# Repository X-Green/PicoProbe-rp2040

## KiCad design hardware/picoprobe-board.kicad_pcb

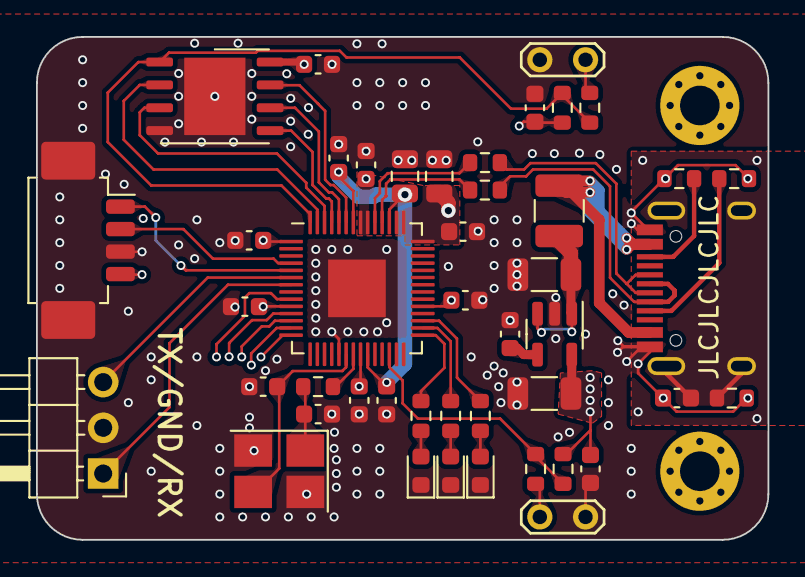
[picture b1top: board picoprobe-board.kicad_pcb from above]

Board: 4 copper layers, 40.6 x 27.9 mm, 47 parts (0 on the bottom side), 35 nets.

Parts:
C1, C2, C5, C6, C7, C8, C9, C10, C11, C12: 100nF; C_0603_1608Metric
C3: 1uF; C_0603_1608Metric
C4, C14: 2.2uF; C_0805_2012Metric
C15: 10uF; C_1206_3216Metric
C16, C18: 10nF; C_0603_1608Metric
C17: 2.2uF; C_1206_3216Metric
C19, C20: 12pF; C_0603_1608Metric
D1, D2, D3: LED; LED_0603_1608Metric
F1: Fuse; Fuse_1210_3225Metric
H1, H2: MountingHole_Pad; MountingHole_2.2mm_M2_Pad_Via
J1: Conn_01x03_MountingPin; PinHeader_1x03_P2.54mm_Horizontal
J2: USB_C_Receptacle_USB2.0; USB_C_Receptacle_HRO_TYPE-C-31-M-12
J3: Conn_01x04_MountingPin; Molex_PicoBlade_53261-0471_1x04-1MP_P1.25mm_Horizontal
JP1, JP2: Jumper_2_Open; TestPoint_2Pads_Pitch2.54mm_Drill0.8mm
R1, R3: 10K; R_0603_1608Metric
R2, R4: 1K; R_0603_1608Metric
R5: 470R; R_0603_1608Metric
R6, R7: 27.4R; R_0603_1608Metric
R9, R10, R11: 4.7K; R_0603_1608Metric
R14, R15: 5.1k; R_0603_1608Metric
R16: 1M; R_0603_1608Metric
U1: W25Q32JVZP; WSON-8-1EP_6x5mm_P1.27mm_EP3.4x4.3mm
U2: RP2040; QFN-56-1EP_7x7mm_P0.4mm_EP3.2x3.2mm
U3: RT9013-33GB; TSOT-23-5
Y2: Crystal_GND24; Crystal_SMD_3225-4Pin_3.2x2.5mm_HandSoldering

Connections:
+3V3: C1.2, C2.1, C3.2, C7.2, C8.2, C9.2, C10.2, C11.2, C12.2, C14.2, C17.1, J3.4, R1.1, R3.1, U1.8 (VCC), U2.1 (IOVDD), U2.10 (IOVDD), U2.22 (IOVDD), U2.33 (IOVDD), U2.42 (IOVDD), U2.43 (ADC_AVDD), U2.44 (VREG_IN), U2.48 (USB_VDD), U2.49 (IOVDD), U3.5 (VOUT)
+5V: C15.1, F1.1, U3.1 (VIN), U3.3 (EN)
/QSPI_CLK: U1.6 (CLK), U2.52 (QSPI_SCLK)
/QSPI_SD0: U1.5 (DI(IO0)), U2.53 (QSPI_SD0)
/QSPI_SD1: U1.2 (DO(IO1)), U2.55 (QSPI_SD1)
/QSPI_SD2: U1.3 (IO2), U2.54 (QSPI_SD2)
/QSPI_SD3: U1.7 (IO3), U2.51 (QSPI_SD3)
/QSPI_SS: R1.2, R2.2, U1.1 (~CS), U2.56 (QSPI_SS)
/RUN: R3.2, R4.1, U2.26 (RUN)
/SWCLK: J3.2, U2.4 (GPIO2)
/SWDIO: J3.1, U2.5 (GPIO3)
/UART1_RX: J1.1, U2.7 (GPIO5)
/UART1_TX: J1.3, U2.6 (GPIO4)
/USB_DM: J2.A7 (D-), J2.B7 (D-), R7.1
/USB_DP: J2.A6 (D+), J2.B6 (D+), R6.1
/VREG: C4.2, C5.2, C6.2, U2.23 (DVDD), U2.45 (VREG_VOUT), U2.50 (DVDD)
GND: C1.1, C2.2, C3.1, C4.1, C5.1, C6.1, C7.1, C8.1, C9.1, C10.1, C11.1, C12.1, C14.1, C15.2, C16.2, C17.2, C18.1, C19.2, C20.2, D1.1 (K), D2.1 (K), D3.1 (K), J1.2, J2.A1 (GND), J2.A12 (GND), J2.B1 (GND), J2.B12 (GND), J3.3, J3.MP (MountPin), JP1.1 (A), JP2.1 (A), R14.1, R15.1, R16.1, U1.4 (GND), U1.9 (EP), U2.19 (TESTEN), U2.57 (GND), U3.2 (GND), Y2.2, Y2.4
unnamed: C20.1, R5.1, Y2.1
unnamed: D1.2 (A), R9.1
unnamed: D2.2 (A), R10.1
unnamed: D3.2 (A), R11.1
unnamed: F1.2, J2.A4 (VBUS), J2.A9 (VBUS), J2.B4 (VBUS), J2.B9 (VBUS)
unnamed: J2.A5 (CC1), R14.2
unnamed: J2.B5 (CC2), R15.2
unnamed: C18.2, J2.S1 (SHIELD), R16.2
unnamed: JP1.2 (B), R2.1
unnamed: JP2.2 (B), R4.2
unnamed: R9.2, U2.29 (GPIO18)
unnamed: R10.2, U2.30 (GPIO19)
unnamed: R11.2, U2.31 (GPIO20)
unnamed: R7.2, U2.46 (USB_DM)
unnamed: R6.2, U2.47 (USB_DP)
unnamed: C19.1, U2.20 (XIN), Y2.3
unnamed: R5.2, U2.21 (XOUT)
unnamed: C16.1, U3.4 (SENSE/ADJ)

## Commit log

2023-04-12 ver1 done
